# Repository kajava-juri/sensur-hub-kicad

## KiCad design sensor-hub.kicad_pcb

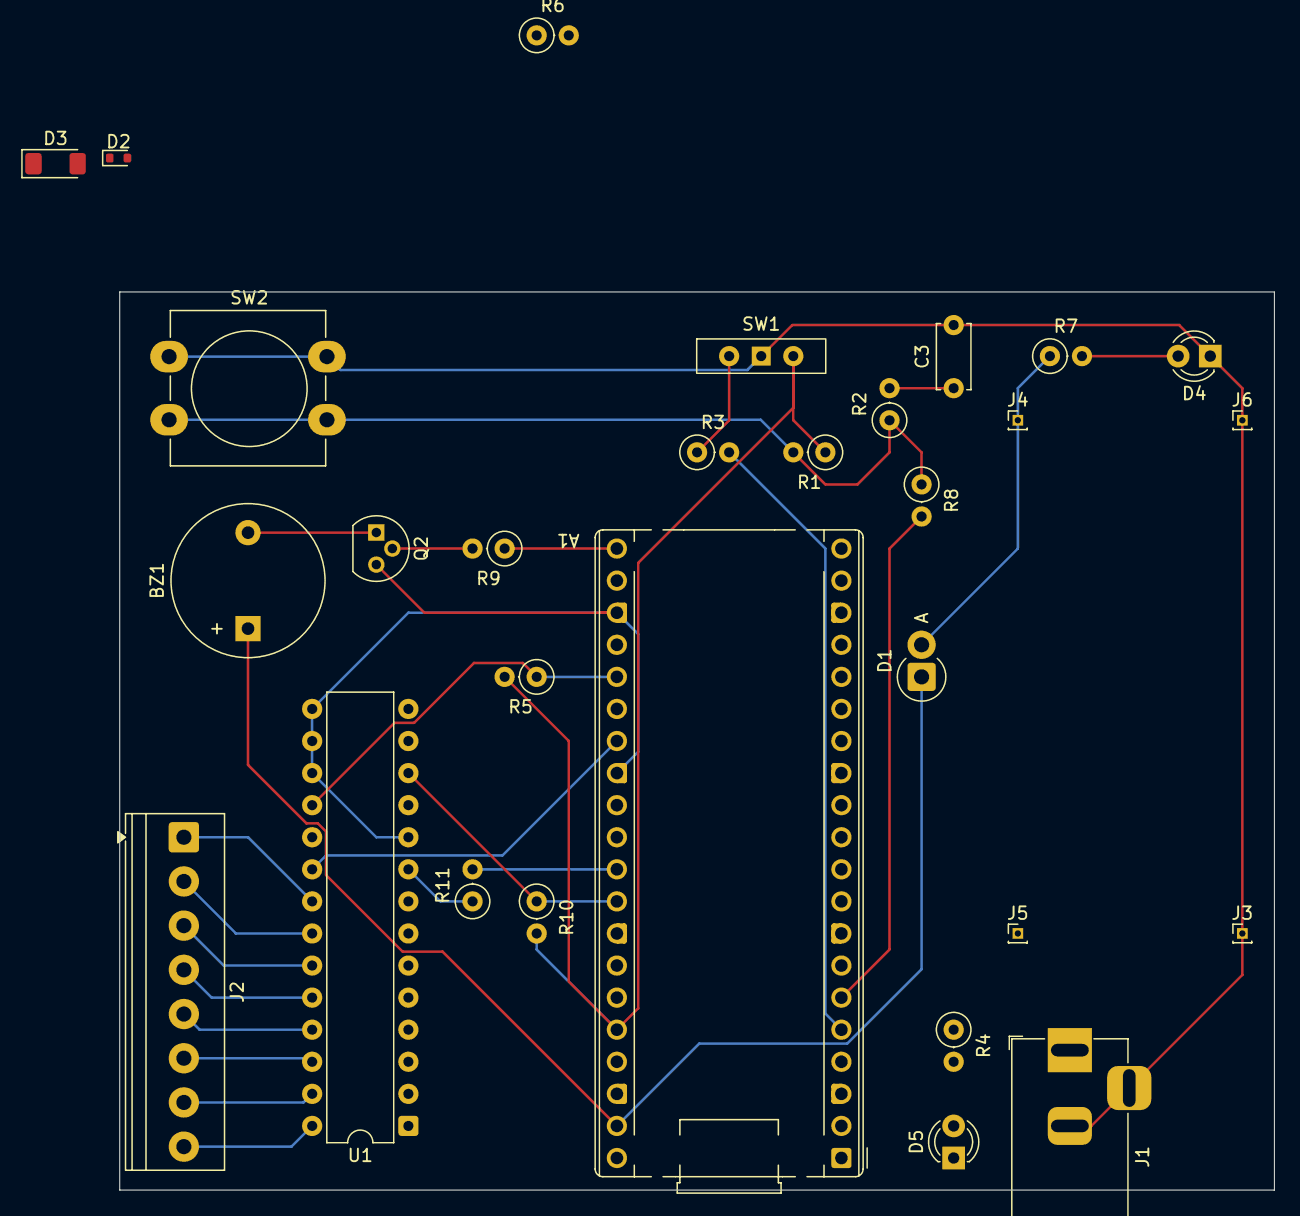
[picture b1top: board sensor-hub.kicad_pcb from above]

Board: 2 copper layers, 91.4 x 71.1 mm, 29 parts (0 on the bottom side), 29 nets.

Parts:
A1: RaspberryPi_Pico_W; RaspberryPi_Pico_Common_THT
BZ1: Buzzer; Buzzer_12x9.5RM7.6
C3: 0,1u; C_Disc_D5.0mm_W2.5mm_P5.00mm
D1: D_Schottky; D_DO-15_P2.54mm_Vertical_AnodeUp
D2: ESD5Zxx; D_SOD-523
D3: BZV55B12; D_MiniMELF
D4, D5: LED; LED_D3.0mm
J1: Barrel_Jack_Switch; BarrelJack_Horizontal
J2: Screw_Terminal_01x08; TerminalBlock_Phoenix_PT-1,5-8-3.5-H_1x08_P3.50mm_Horizontal
J3, J4, J5, J6: 01x01_Pin; PinHeader_1x01_P1.00mm_Vertical
Q2: NPN; TO-92
R1, R5, R6: 10k; R_Axial_DIN0207_L6.3mm_D2.5mm_P2.54mm_Vertical
R2, R3, R4, R7, R8, R9: 1k; R_Axial_DIN0207_L6.3mm_D2.5mm_P2.54mm_Vertical
R10, R11: 4,7k; R_Axial_DIN0207_L6.3mm_D2.5mm_P2.54mm_Vertical
SW1: SW_SPDT; SW_Slide-03_Wuerth-WS-SLTV_10x2.5x6.4_P2.54mm
SW2: SW_SPST; SW_PUSH-12mm_Wuerth-430476085716
U1: MCP23017_SP; DIP-28_W7.62mm

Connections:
+3.3V: A1.36 (3V3), R1.1, R5.2, R10.2, R11.1, SW1.3 (C), U1.9 (VDD)
/+5V_A: A1.39 (VSYS), BZ1.1 (+), D1.1 (K)
/+5V_A_PRES: D1.2 (A), J4.1, R7.1
/A0_IN: J2.1, U1.21 (GPA0)
/A1_IN: J2.2, U1.22 (GPA1)
/A2_IN: J2.3, U1.23 (GPA2)
/A3_IN: J2.4, U1.24 (GPA3)
/A4_IN: J2.5, U1.25 (GPA4)
/A5_IN: J2.6, U1.26 (GPA5)
/A6_IN: J2.7, U1.27 (GPA6)
/A7_IN: J2.8, U1.28 (GPA7)
/ARM_DISARM: A1.5 (GPIO3), R3.2
/BUZZER: A1.21 (GPIO16), R9.1
/INTA: A1.27 (GPIO21), U1.20 (INTA)
/MCP_RESET: A1.25 (GPIO19), R5.1, U1.18 (~RESET)
/RESET_SW: A1.6 (GPIO4), R8.2
/SCK: A1.32 (GPIO27_ADC1), R10.1, U1.12 (SCK)
/SDA: A1.31 (GPIO26_ADC0), R11.2, U1.13 (SDA)
/VIN_PROT: D3.1 (K), J5.1
/VIN_RAW: D2.1 (K), J1.1, R4.1
GND: A1.3 (GND), A1.8 (GND), A1.13 (GND), A1.18 (GND), A1.23 (GND), A1.28 (GND), A1.38 (GND), C3.2, D2.2 (A), D4.1 (K), D5.1 (K), J1.2, J1.3, J3.1, J6.1, Q2.3 (E), R6.2, SW1.1 (A), SW2.1 (A), U1.10 (VSS), U1.15 (A0), U1.16 (A1), U1.17 (A2)
unnamed: BZ1.2 (-), Q2.1 (C)
unnamed: C3.1, R2.2
unnamed: D3.2 (A), R6.1
unnamed: D4.2 (A), R7.2
unnamed: D5.2 (A), R4.2
unnamed: Q2.2 (B), R9.2
unnamed: R3.1, SW1.2 (B)
unnamed: R1.2, R2.1, R8.1, SW2.2 (B)

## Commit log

2025-12-14 init
2025-12-23 power good leds, buzzer control, other minor stuff for convenience
2025-12-25 v1 ready with a perfboard placement in pcb editor planned out
